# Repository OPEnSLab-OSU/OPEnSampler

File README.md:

# OPEnSampler
Code and materials for OPEnSampler bottle version: an Open-Source, inexpensive peristaltic pump-driven, sampler device.

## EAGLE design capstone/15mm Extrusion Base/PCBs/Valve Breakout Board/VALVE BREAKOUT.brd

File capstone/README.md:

# OPEnSampler (Capstone Fork)

The OPEnSampler is an openly published water sampler designed with a focus on
customizability. The device was designed in Autodesk Fusion 360, a free CAD software for
any student or startup with low profits, specified by their terms for the license.

The main features include an Arduino-controlled array of solenoid valves to manage the
sample water flow and a 12VDC peristaltic pump, an extruded aluminum frame and 3D printed
components for attaching the valves, bags, pump, and electronics to the device.
The OPEnSampler fits in a Pelican 80QT Rolling Cooler and is powered from a 12VDC battery.

Check out our blog for updates and more information!

**Blog:** http://www.open-sensing.org/watersamplerblog/

**Fusion 360:** https://www.autodesk.com/products/fusion-360/students-teachers-educators

**OPEnS Lab Website:** http://www.open-sensing.org/

**OPEnS Lab Facebook:** https://www.facebook.com/open.sensing/

## Capstone

This folder is a fork of the OPEnSampler project built on by members of an Oregon State
University CS Capstone group, working in collaboration with OPEnS Lab.
This project enhances the OPEnSampler by adding support for sending text messages (SMS) to
send information to users, and by developing an Android app that can configure the sampler
over Bluetooth. 

## Dependencies

The following dependencies are available in `ArduinoCode/Libraries`.
To install them, follow the [instructions for installing libraries in Arduino
IDE](https://www.arduino.cc/en/guide/libraries#toc4).

* [Adafruit FONA](https://github.com/adafruit/Adafruit_FONA.git) for sending SMS
  status updates.
* [Adafruit nRF8001](https://github.com/adafruit/Adafruit_nRF8001.git) for
  communicating with the OPEnSampler Companion App over Bluetooth Low Energy.
* [EEPROMWriteAnything](http://playground.arduino.cc/Code/EEPROMWriteAnything)
  for writing the OPEnSampler's configuration to EEPROM. (This is included
  directly within the Skectchbook.)
* [Low-Power](https://github.com/rocketscream/Low-Power) for sleeping in
  between samples.
* [RTClibExtended](https://github.com/FabioCuomo/FabioCuomo-DS3231) for
  interrupt alarms that wake the OPEnSampler from sleeping.

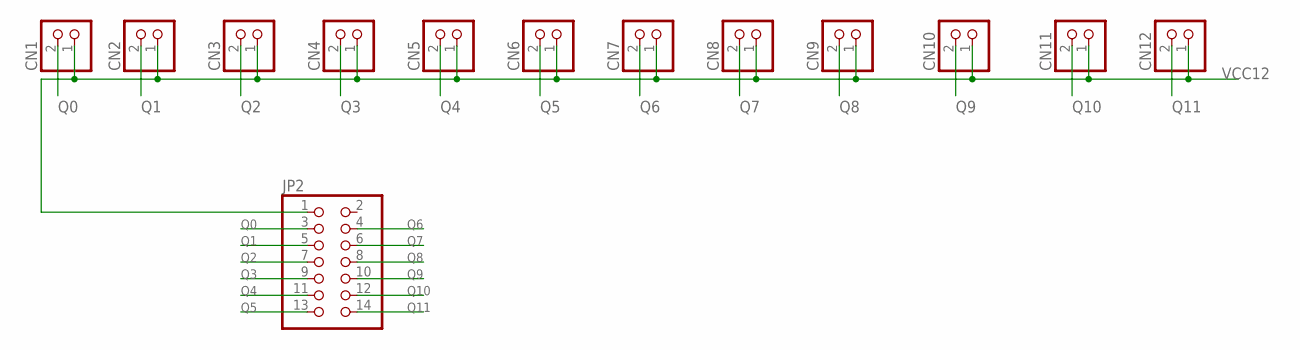
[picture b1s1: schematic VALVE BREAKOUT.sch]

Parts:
CN1, CN2, CN3, CN4, CN5, CN6, CN7, CN8, CN9, CN10, CN11, CN12: JST_2PIN-THM; JST-PH-2-THM
JP2: PINHD-2X7; 2X07

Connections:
Q0: CN1.2 (1), JP2.3
Q1: CN2.2 (1), JP2.5
Q2: CN3.2 (1), JP2.7
Q3: CN4.2 (1), JP2.9
Q4: CN5.2 (1), JP2.11
Q5: CN6.2 (1), JP2.13
Q6: CN7.2 (1), JP2.4
Q7: CN8.2 (1), JP2.6
Q8: CN9.2 (1), JP2.8
Q9: CN10.2 (1), JP2.10
Q10: CN11.2 (1), JP2.12
Q11: CN12.2 (1), JP2.14
VCC12: CN1.1 (2), CN2.1 (2), CN3.1 (2), CN4.1 (2), CN5.1 (2), CN6.1 (2), CN7.1 (2), CN8.1 (2), CN9.1 (2), CN10.1 (2), CN11.1 (2), CN12.1 (2), JP2.1

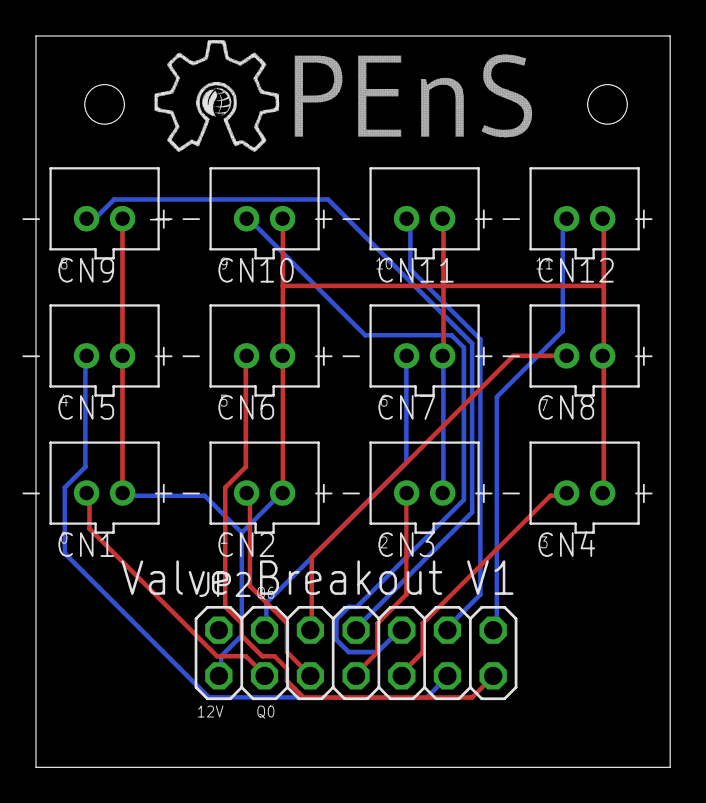
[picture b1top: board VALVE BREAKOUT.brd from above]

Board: 2 copper layers, 35.2 x 40.6 mm, 14 parts (0 on the bottom side), 13 nets.

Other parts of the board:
U$1: OPENS-LOGO

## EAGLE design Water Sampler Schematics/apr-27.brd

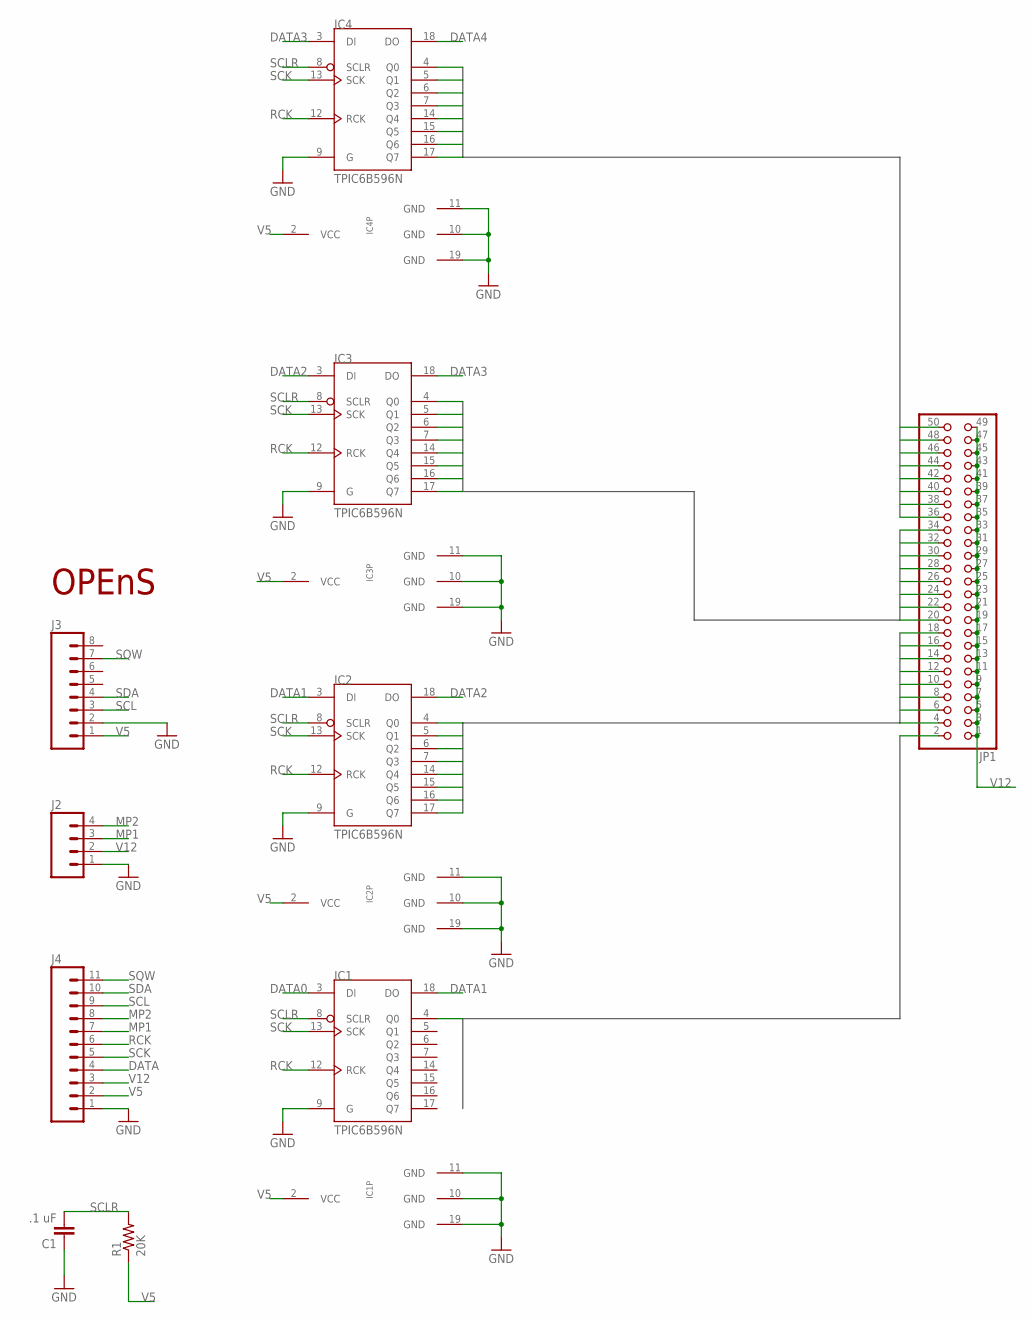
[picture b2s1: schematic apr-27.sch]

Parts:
C1: .1 uF; AXIAL-5MM
IC1, IC2, IC3, IC4: TPIC6B596N; DIL20
J2: M04PTH; 1X04
J3: M08; 1X08_ROUND
J4: M11PTH; 1X11
JP1: PINHD-2X25; 2X25
R1: 20K; AXIAL-0.4
U$1: OPENS-LOGO

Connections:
DATA: J4.4
DATA0: IC1.3 (DI)
DATA1: IC1.18 (DO), IC2.3 (DI)
DATA2: IC2.18 (DO), IC3.3 (DI)
DATA3: IC3.18 (DO), IC4.3 (DI)
DATA4: IC4.18 (DO)
GND: C1.P$1 (1), IC1.9 (G), IC1.10 (GND), IC1.11 (GND), IC1.19 (GND), IC2.9 (G), IC2.10 (GND), IC2.11 (GND), IC2.19 (GND), IC3.9 (G), IC3.10 (GND), IC3.11 (GND), IC3.19 (GND), IC4.9 (G), IC4.10 (GND), IC4.11 (GND), IC4.19 (GND), J2.1, J3.2, J4.1
MP1: J2.3, J4.7
MP2: J2.4, J4.8
Q0: IC1.4 (Q0), JP1.2
Q1: IC2.4 (Q0), JP1.4
Q2: IC2.5 (Q1), JP1.6
Q3: IC2.6 (Q2), JP1.8
Q4: IC2.7 (Q3), JP1.10
Q5: IC2.14 (Q4), JP1.12
Q6: IC2.15 (Q5), JP1.14
Q7: IC2.16 (Q6), JP1.16
Q8: IC2.17 (Q7), JP1.18
Q9: IC3.4 (Q0), JP1.20
Q10: IC3.5 (Q1), JP1.22
Q11: IC3.6 (Q2), JP1.24
Q12: IC3.7 (Q3), JP1.26
Q13: IC3.14 (Q4), JP1.28
Q14: IC3.15 (Q5), JP1.30
Q15: IC3.16 (Q6), JP1.32
Q16: IC3.17 (Q7), JP1.34
Q17: IC4.4 (Q0), JP1.36
Q18: IC4.5 (Q1), JP1.38
Q19: IC4.6 (Q2), JP1.40
Q20: IC4.7 (Q3), JP1.42
Q21: IC4.14 (Q4), JP1.44
Q22: IC4.15 (Q5), JP1.46
Q23: IC4.16 (Q6), JP1.48
Q24: IC4.17 (Q7), JP1.50
RCK: IC1.12 (RCK), IC2.12 (RCK), IC3.12 (RCK), IC4.12 (RCK), J4.6
SCK: IC1.13 (SCK), IC2.13 (SCK), IC3.13 (SCK), IC4.13 (SCK), J4.5
SCL: J3.3, J4.9
SCLR: C1.P$2 (2), IC1.8 (SCLR), IC2.8 (SCLR), IC3.8 (SCLR), IC4.8 (SCLR), R1.P$2 (2)
SDA: J3.4, J4.10
SQW: J3.7, J4.11
V5: IC1.2 (VCC), IC2.2 (VCC), IC3.2 (VCC), IC4.2 (VCC), J3.1, J4.2, R1.P$1 (1)
V12: J2.2, J4.3, JP1.1, JP1.3, JP1.5, JP1.7, JP1.9, JP1.11, JP1.13, JP1.15, JP1.17, JP1.19, JP1.21, JP1.23, JP1.25, JP1.27, JP1.29, JP1.31, JP1.33, JP1.35, JP1.37, JP1.39, JP1.41, JP1.43, JP1.45, JP1.47, JP1.49

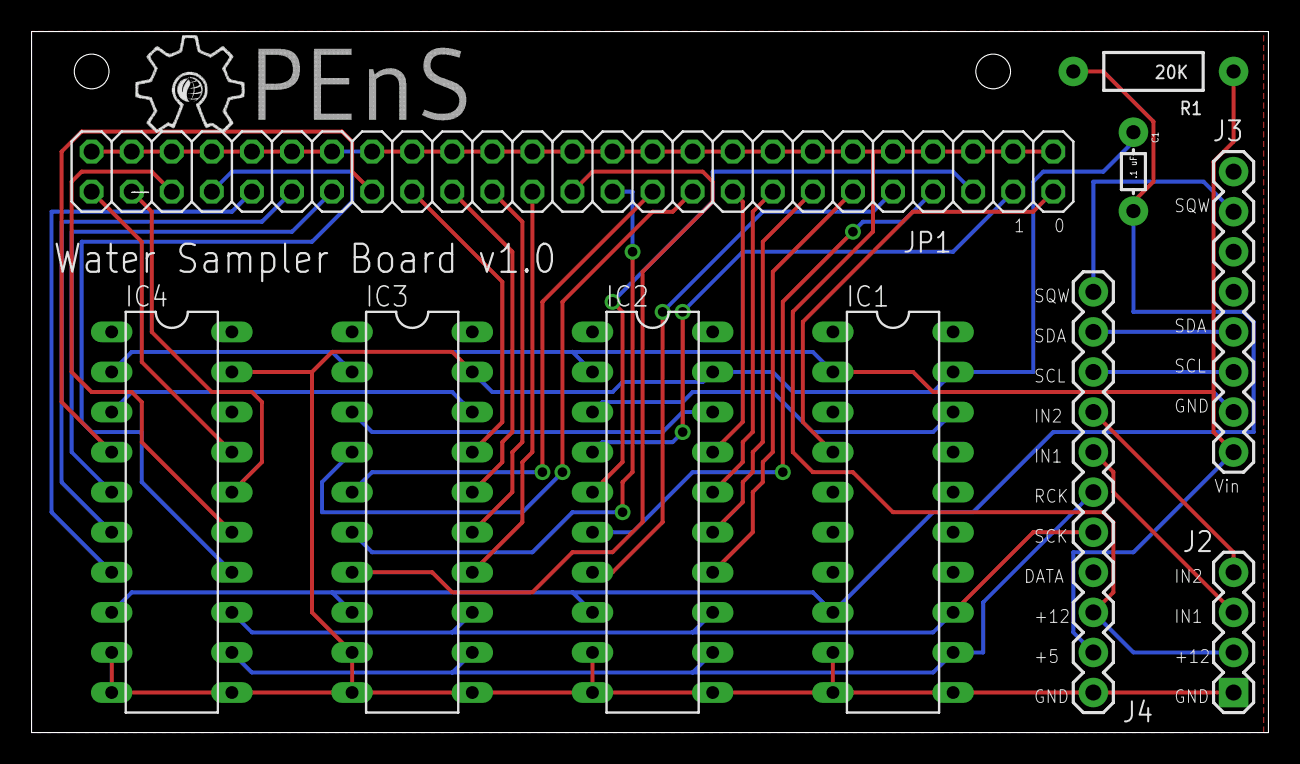
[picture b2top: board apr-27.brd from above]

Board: 2 copper layers, 78.4 x 44.4 mm, 11 parts (0 on the bottom side), 39 nets.

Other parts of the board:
E$1: OPENS-LOGO

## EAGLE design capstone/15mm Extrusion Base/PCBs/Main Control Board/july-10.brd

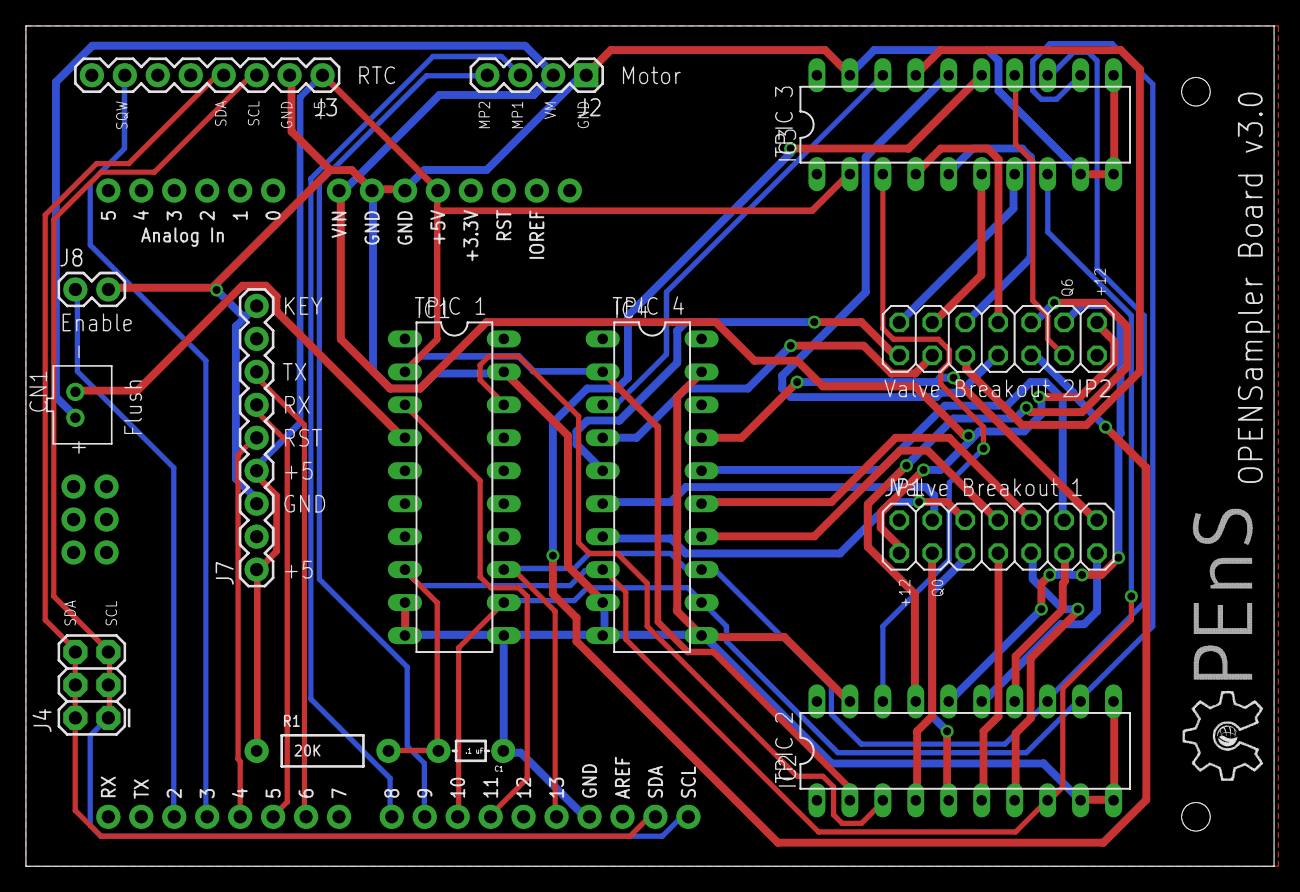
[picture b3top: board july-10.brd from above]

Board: 2 copper layers, 96.2 x 64.8 mm, 16 parts (0 on the bottom side), 44 nets.

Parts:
C1: .1 uF; AXIAL-5MM
CN1: JST-PH-2-THM
IC1, IC2, IC3, IC4: TPIC6B596N; DIL20
J2: 1X04
J3: 1X08_ROUND
J4: FEMALE 2x3; 2X3
J6: ARDUINO_R3_SHIELD_ICSP; UNO_R3_SHIELD_ICSP
J7: 1X09
J8: 1X02
JP1, JP2: 2X07
R1: 20K; AXIAL-0.4
U$1: OPENS-LOGO

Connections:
DATA0: IC1.3, J6.D11
DATA1: IC1.18, IC2.3
DATA2: IC2.18, IC3.3
DATA3: IC3.18, IC4.3
GND: C1.P$1, IC1.9, IC1.10, IC1.11, IC1.19, IC2.9, IC2.10, IC2.11, IC2.19, IC3.9, IC3.10, IC3.11, IC3.19, IC4.9, IC4.10, IC4.11, IC4.19, J2.1, J3.2, J6.GND@0, J6.GND@1, J6.GND@2, J7.3, J7.9, J8.2
GSM_RESET: J6.D4, J7.5
GSM_RX: J6.D5, J7.6
GSM_TX: J6.D6, J7.7
MP1: J2.3, J6.D8
MP2: J2.4, J6.D9
unnamed: CN1.2, IC1.4
unnamed: J6.D2, J8.1
Q0: IC2.4, JP1.3
Q1: IC2.5, JP1.5
Q2: IC2.6, JP1.7
Q3: IC2.7, JP1.9
Q4: IC2.14, JP1.11
Q5: IC2.15, JP1.13
Q6: IC2.16, JP2.3
Q7: IC2.17, JP2.5
Q8: IC3.4, JP2.7
Q9: IC3.5, JP2.9
Q10: IC3.6, JP2.11
Q11: IC3.7, JP2.13
Q12: IC3.14, JP2.4
Q13: IC3.15, JP2.6
Q14: IC3.16, JP2.8
Q15: IC3.17, JP2.10
Q16: IC4.4, JP2.12
Q17: IC4.5, JP2.14
Q18: IC4.6, JP1.4
Q19: IC4.7, JP1.6
Q20: IC4.14, JP1.8
Q21: IC4.15, JP1.10
Q22: IC4.16, JP1.12
Q23: IC4.17, JP1.14
RCK: IC1.12, IC2.12, IC3.12, IC4.12, J6.D10
SCK: IC1.13, IC2.13, IC3.13, IC4.13, J6.D13
SCL: J3.3, J4.1, J4.3, J4.5, J6.SCL
SCLR: C1.P$2, IC1.8, IC2.8, IC3.8, IC4.8, R1.P$2
SDA: J3.4, J4.2, J4.4, J4.6, J6.SDA
SQW: J3.7, J6.D3
V5: IC1.2, IC2.2, IC3.2, IC4.2, J3.1, J6.5V, J7.1, J7.4, R1.P$1
V12: CN1.1, J2.2, J6.VIN, JP1.1, JP2.1

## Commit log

2017-10-17 Added blank android studio project with compatibility for Android 5.0 and up
2017-10-17 Update .gitignore for Android Studio project.
2017-11-07 Unified and cleaned up duplicates for prior 2 split repositories.
    Took all files from WaterSampler repository except Arduino code since that was a prior version. Unzipped Arduino code to make more transparent versioning.
2017-11-14 Updated to OPEnSampler Q4 2017
    Removed irrelevant files that didn't need to be shared. Removed OPEnSampler 4040 files and replaced with OPEnSampler Q4 2017 files (15mm extrusion). Added CAD files and BoM, along with Printed Compon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
2017-11-14 README to plain text
    the rich text file was displaying poorly on the GitHub repo.
2018-01-17 Beginning UI Design
2018-01-17 Re-adding files
2018-01-24 Add serial commands for reading/writing phone numbers.
    * Adds an array of phone numbers to configuration (stored in EEPROM).
    * Adds two serial commands: PR <index>
    PW <index> <phone number>
    * Cleans up serial command state machine indentation/ordering
2018-01-25 Updating the OpenSampler Companion App
2018-02-05 Updated the Schedule UI to incorporate a timepicker, now ready for sending bluetooth commands
2018-02-05 Refactor serial commands to separate input from functionality.
2018-02-07 Elements are now clickable inside fragments
2018-02-15 Created folder to store flowchart state machine diagrams of code
2018-02-15 State Machine Diagrams of OPEnSampler code added
2018-03-04 Add new libraries as git submodules.
2018-03-04 Move dependency info from sketch to README.
    Adds README content from upstream with list of dependencies.
    Also removes some old changelog info from the sketch. (Changelog file
    would be better.)
2018-03-04 Fix spacing between links in README.md
2018-03-08 Huge Changes to the GUI
2018-03-13 finished bluetooth conection
2018-03-13 final files for bt
2018-03-13 gradle update
2018-03-14 added copyright notice for nordic code used in creation of the project
2018-03-14 more copyright stuff
2018-03-14 added some clarifying comments, cleaned up the code a little bit
2018-03-14 cleanup
2018-03-18 Add BLE command parser & refactor configuration into class.
    This commit adds BLE functionality and a new command parser for use with
    the Companion App. The other major change is that instead of having a
    global configuration struct, it's been refactored into a class (with
    methods for manipulating the configuration).
    This also includes some reference docs of the commands useable over
    Serial & BLE.
2018-03-21 Remove debugging code.
    Removes a test for the CommandParser class, and tweaks the BLEParser's default terminating & delimiting characters.
2018-03-21 Properly remove git submodules.
    Tried to use git submodules for the libraries, but it's unideal.
    Thought I had removed it properly, but I guess not.
2018-03-22 Added Eagle PCB Files for March 2018 iteration.
2018-03-22 Moved eagle files
    Moved eagle files to new 2018 Q1 folder
    Removed unnecessary old schematic files
2018-04-04 Replace magic number with constant for phone number length.
2018-04-04 Add debugging code and minor cleanup.
2018-04-04 Save WIP debug code for sending config over BLE.
2018-04-04 added sch file
2018-04-06 Add status update code.
2018-04-06 Remove PinChangeInterrupt.
    Although this library was previously the solution to our interrupt pin
    limitations, it turns out it doesn't work with SoftwareSerial (which is
    a dependency for Adafruit FONA 808):
    https://github.com/NicoHood/PinChangeInterrupt/issues/14#issuecomment-300697665
    This doesn't really matter if OPEnS Lab is moving from the Uno R3 to the
    Feather, anyways.
2018-04-06 Add SMS status update events.
2018-04-13 REBASE ME: Save state before commenting out library objects.
2018-04-14 Store all static strings in flash memory.
2018-04-25 Initial incomplete incorporation of timed sequence functions
    Timed sequences use arrays of functions, times, and sequences to step through actions over specified times and orders. Added AsyncDelay library for timing instead of millis(). Goal is to create adapt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
2018-04-27 fixed broadcast manager, actually manages now Please enter the commit message for your changes. Lines starting
2018-04-27 Fixed Fragment Manager
    Switched the buttons to be weighted inside a linear layout in order to
    allow for all phone screen sizes
2018-04-27 Updated and fixed the FragmentManager
2018-04-27 Revert "Updated button"
2018-05-02 Testing functions
    Added sketch for running tests on sampler
2018-05-03 Switched valve addressing scheme, modular TPIC number
    Added code to allow for number of bags other than 24. Simplified what is being sent to TPICs.
2018-05-04 Tweak some comments.
2018-05-04 Bug fix for testing sketch
    Program doesn't error out anymore, but only flush valve is opening.
2018-05-04 Updated Connection Page to be the Puppet Page
2018-05-07 Fix CommandParser bug with multiple args.
    And some cleanup.
2018-05-09 Remove accidentally committed swapfile
2018-05-09 Fix compiler warnings.
2018-05-09 NetworkStatus enum, DEBUG define, and const keywords.
    * Add a NetworkStatus enum so StatusUpdate's network state logic is
    easier to interpret
    * Add a DEBUG definition so prints for debugging don't have to be
    compiled in
    * Correct char pointers to const char pointers
2018-05-12 Lots of last minute cleanup! Looking good~
2018-05-12 Updated Phone Frag to now send phone commands
2018-06-05 TPIC addressing fixed
2018-06-05 Remove accidentally committed .vscode folder
2018-06-06 Remove old codebase and update README slightly
2018-06-07 Add to API documentation and README
2018-06-07 Fix clock example in OPEnSampler API documentation
2018-06-08 Code tidied and preliminary prime sequence with unrefined timing.
2018-06-09 Slight cleanup
2018-06-09 Move capstone-related work into capstone folder
2018-06-09 Added Comments to most .java classes
2018-06-09 Removed Connection Screen
2018-06-09 Removed Connection Button from Fragment Manager
    First screen seen is the scheduler, where users can connect to the
    OpenSampler device
2018-06-09 removed files and started commenting
2018-06-09 added comments and ble functionality to the puppet screen
2018-06-09 Move remnants of cherry-picking to capstone folder
2018-06-09 Remove .idea (IDE-specific config)
2018-06-09 Remove .gitignore
2018-10-24 Initial folder reorganization after branch merging
2018-10-27 Initial combination of altTPICcode and Capstone.
    Issues with variables not being declared across tabs. Added flash.h and code from Sleep_RTC from OPEnS IoA. Minor modifications for M0.
2018-11-10 Eliminated a couple of files, did some tidying, still lots of errors
2018-11-14 Re-established header files - need to work on scope from Definitions.h
2020-08-28 Final components
    Final code and components for bottle version of sampler.
2020-08-28 Small updated in comments

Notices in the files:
parts and their libraries:
SparkFun-Capacitors: Licensing: Creative Commons ShareAlike 4.0 International - https://creativecommons.org/licenses/by-sa/4.0
